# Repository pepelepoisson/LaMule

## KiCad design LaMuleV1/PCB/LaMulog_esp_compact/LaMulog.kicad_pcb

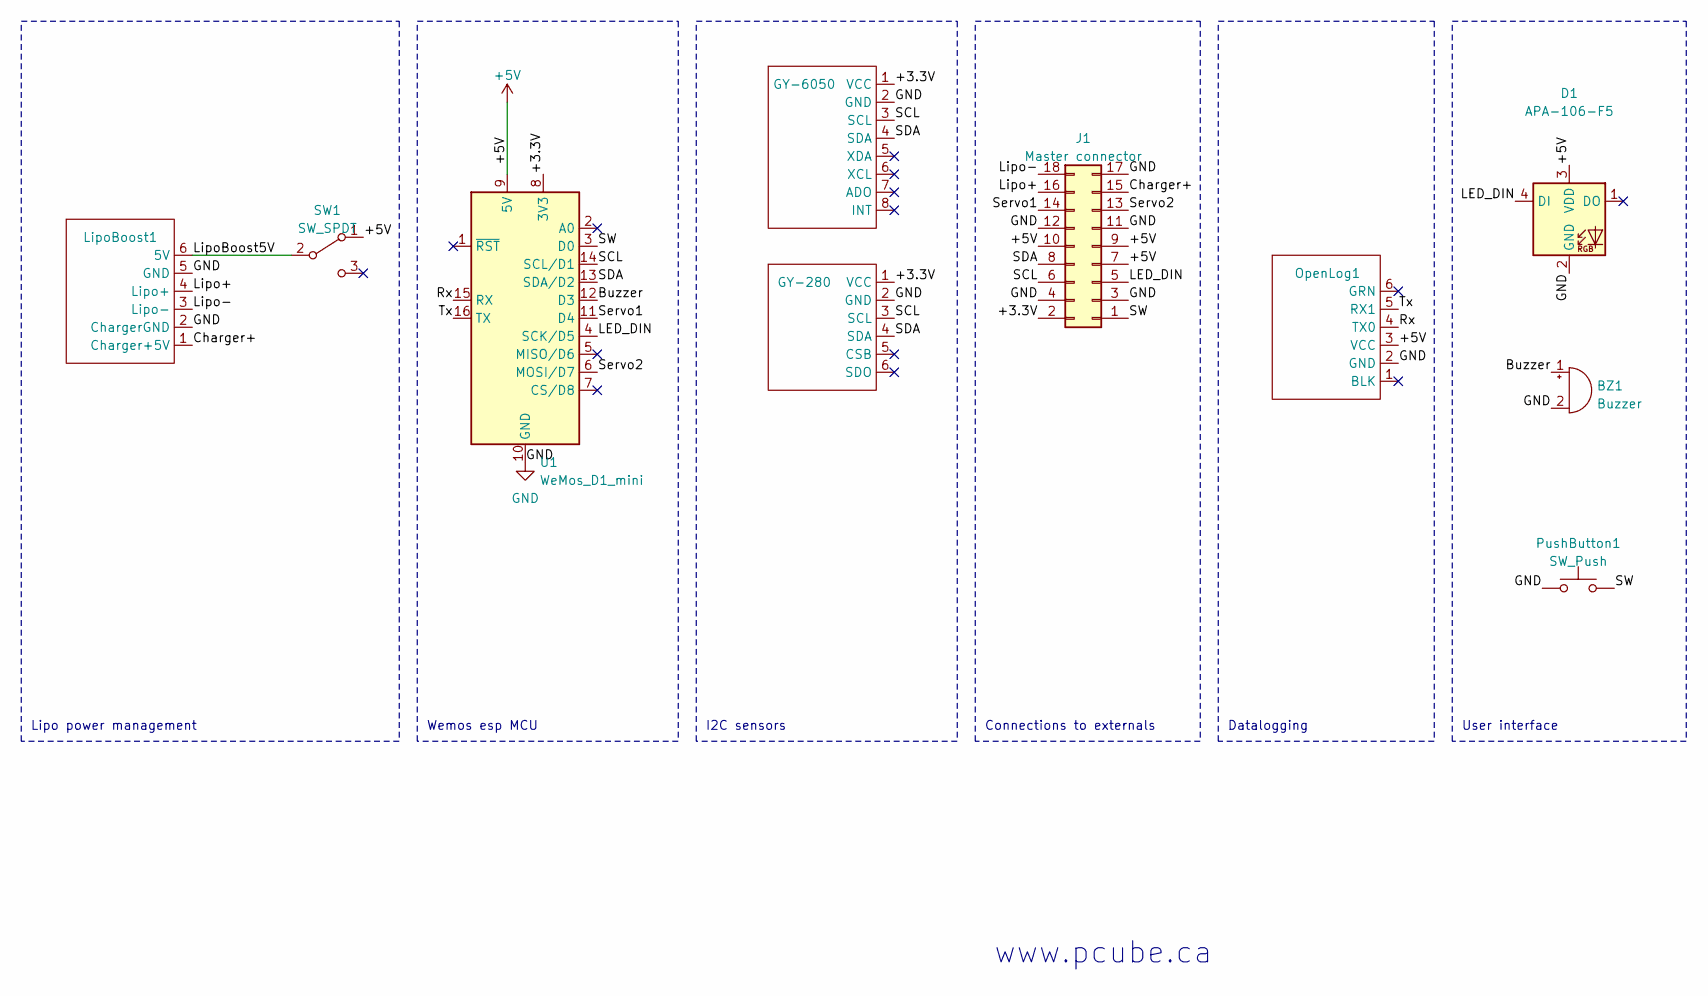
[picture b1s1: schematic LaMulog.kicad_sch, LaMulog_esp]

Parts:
BZ1: Buzzer; Buzzer_12x9.5RM7.6
D1: APA-106-F5; LED_D5.0mm-4_RGB_Wide_Pins
GY-280: GY-280
GY-6050: GY-6050
J1: Master connector; MasterConnectorVertical
LipoBoost1: LipoBoost1
OpenLog1: OpenLog1
PushButton1: SW_Push; SW_Tactile_SPST_Angled_PTS645Vx39-2LFS
SW1: SW_SPDT; Switch
U1: WeMos_D1_mini; WEMOS_D1_mini_light

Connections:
/+3.3V: GY-280.1 (VCC), GY-6050.1 (VCC), J1.2 (Pin_9a), U1.8 (3V3)
/+5V: D1.3 (VDD), J1.7 (Pin_6b), J1.9 (Pin_5b), J1.10 (Pin_5a), OpenLog1.3 (VCC), SW1.1 (A), U1.9 (5V)
/Buzzer: BZ1.1 (-), U1.12 (D3)
/Charger+: J1.15 (Pin_2b), LipoBoost1.1 (Charger+5V)
/LED_DIN: D1.4 (DI), J1.5 (Pin_7b), U1.4 (SCK/D5)
/Lipo+: J1.16 (Pin_2a), LipoBoost1.4 (Lipo+)
/Lipo-: J1.18 (Pin_1a), LipoBoost1.3 (Lipo-)
/LipoBoost5V: LipoBoost1.6 (5V), SW1.2 (B)
/Rx: OpenLog1.4 (TX0), U1.15 (RX)
/SCL: GY-280.3 (SCL), GY-6050.3 (SCL), J1.6 (Pin_7a), U1.14 (SCL/D1)
/SDA: GY-280.4 (SDA), GY-6050.4 (SDA), J1.8 (Pin_6a), U1.13 (SDA/D2)
/SW: J1.1 (Pin_9b), PushButton1.2, U1.3 (D0); also elsewhere on the board
/Servo1: J1.14 (Pin_3a), U1.11 (D4)
/Servo2: J1.13 (Pin_3b), U1.6 (MOSI/D7)
/Tx: OpenLog1.5 (RX1), U1.16 (TX)
GND: BZ1.2 (+), D1.2 (GND), GY-280.2 (GND), GY-6050.2 (GND), J1.3 (Pin_8b), J1.4 (Pin_8a), J1.11 (Pin_4b), J1.12 (Pin_4a), J1.17 (Pin_1b), LipoBoost1.2 (ChargerGND), LipoBoost1.5 (GND), OpenLog1.2 (GND), PushButton1.1, U1.10 (GND); also elsewhere on the board

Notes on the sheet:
Datalogging
Lipo power management
www.pcube.ca
User interface
Wemos esp MCU
I2C sensors
Connections to externals

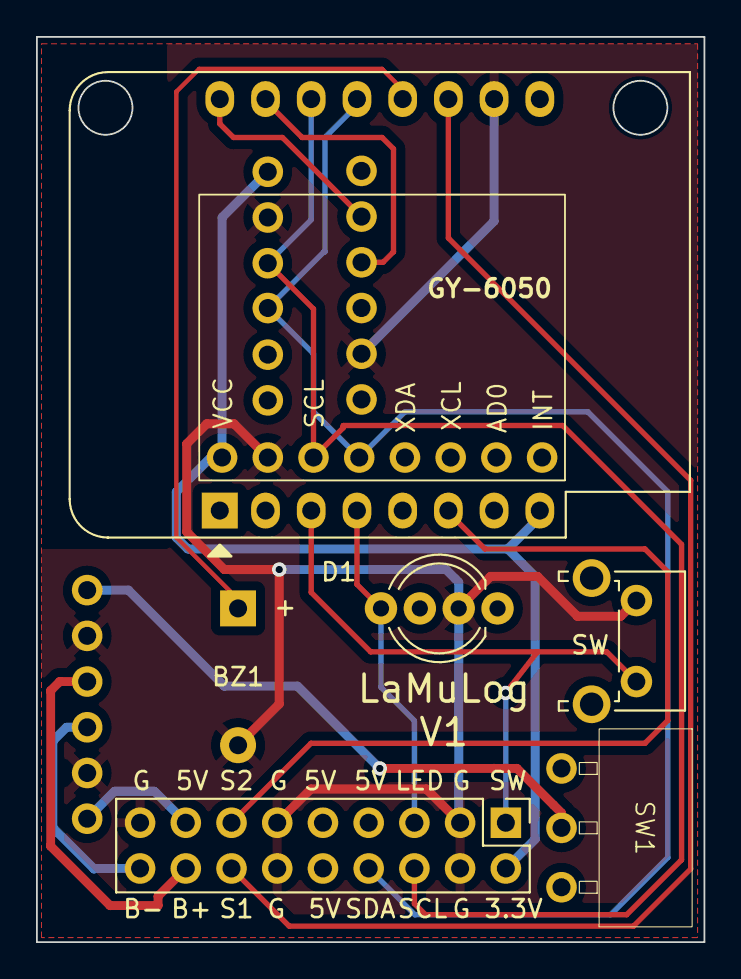
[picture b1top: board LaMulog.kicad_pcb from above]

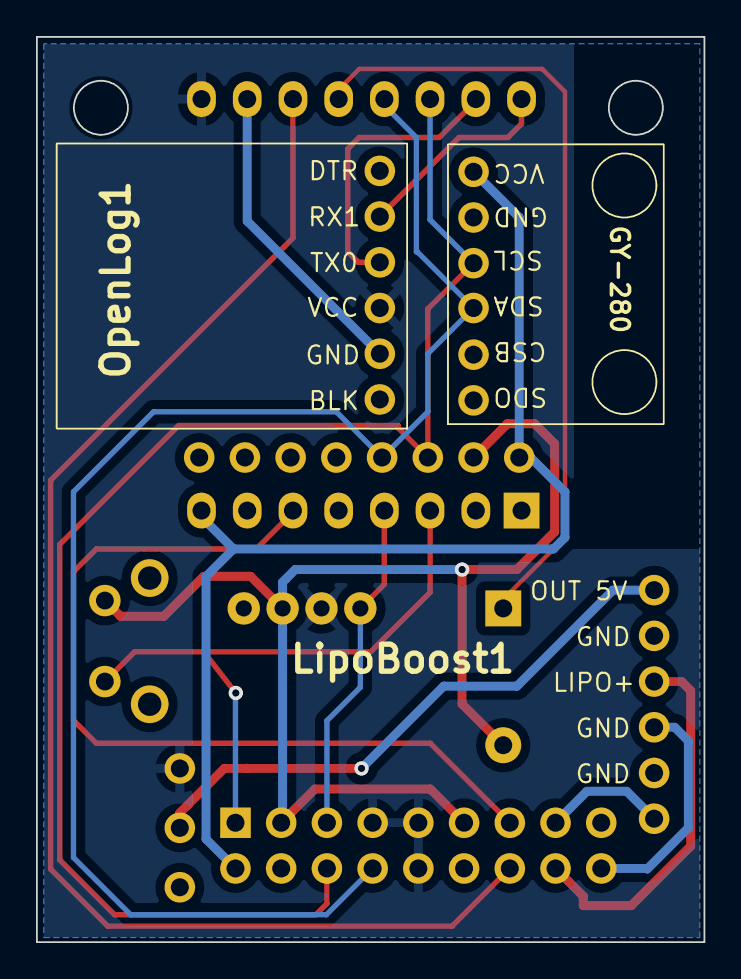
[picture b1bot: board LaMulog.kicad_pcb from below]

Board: 2 copper layers, 37.1 x 50.3 mm, 10 parts (3 on the bottom side), 16 nets.

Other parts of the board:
SW: SW_Push; SW_Tactile_SPST_Angled_PTS645Vx39-2LFS

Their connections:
/SW: SW.2; also elsewhere on the board
GND: SW.1; also elsewhere on the board

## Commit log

2023-12-13 Some cleanup
